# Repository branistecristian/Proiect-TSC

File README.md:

# OpenBook – E-Reader Hardware Project

OpenBook is an open-source e-reader built around the ESP32-C6, featuring a 7.5" e-Paper display, rechargeable battery, and Wi-Fi support. Designed for low-power embedded use and comfortable digital reading.

---

##  Block Diagram

`Images/block_diagram.png`

> Diagram shows how ESP32-C6 is connected to display, battery, charging module, and buttons.

---

## 📋 Bill of Materials (BOM)

| Reference    | Value            | Device                            | Footprint      | Description                      | Link                                                                                             |
|:-------------|:-----------------|:----------------------------------|:---------------|:---------------------------------|:-------------------------------------------------------------------------------------------------|
| BOOT_BUTTON  | BUTTON_CUSYOMV1  | BUTTON_CUSYOMV1                   | MYBUTTON       | -                                | https://industry.panasonic.com/global/en/products/control/switch/light-touch/number/evqpuj02k    |
| C1           | 100nF            | ESP32_WROVER_EAGLE-LTSPICE_CC0402 | C0402          | CAPACITOR, European symbol       | https://componentsearchengine.com/part-view/CC0402MRX5R5BB106/YAGEO                              |
| C2           | 100nF            | ESP32_WROVER_EAGLE-LTSPICE_CC0402 | C0402          | CAPACITOR, European symbol       |                                                                                                  |
| C3           | 100uF TANT       | RCL_CPOL-EUCT3528                 | CT3528         | POLARIZED CAPACITOR              |                                                                                                  |
| C10_SUPERCAP | CPH3225A         | CPH3225A                          | CAPCP3225X100N | 11 mF (EDLC) Supercapacitor 3.3V | https://www.snapeda.com/parts/CPH3225A/Seiko+Instruments/view-part/?ref=eda                      |
| CHG_LED      | -                | ADAFRUIT_LEDCHIP-LED0603          | LED0603        | LED                              | https://www.snapeda.com/parts/KP-1608SURCK/Kingbright/view-part/?ref=search&t=LED                |
| D1           | USBLC6-2SC6Y     | USBLC6-2SC6Y                      | SOT23-6        | TVS Diode Array                  | https://www.snapeda.com/parts/USBLC6-2SC6Y/STMicroelectronics/view-part/?ref=eda                 |
| D2           | -                | AVX_SD0805S020S1R0                | 0805           | Schottky Diode                   | https://eu.mouser.com/ProductDetail/KYOCERA-AVX/SD0805S020S1R0                                   |
| D3           | MBR0530          | MBR0530                           | SOD123         | Schottky Diode                   | https://www.snapeda.com/parts/MBR0530/Onsemi/view-part/?ref=eda                                  |
| D4           | MBR0530          | MBR0530                           | SOD123         | Schottky Diode                   | https://www.snapeda.com/parts/MBR0530/Onsemi/view-part/?ref=eda                                  |
| D5           | MBR0530          | MBR0530                           | SOD123         | Schottky Diode                   | https://www.snapeda.com/parts/MBR0530/Onsemi/view-part/?ref=eda                                  |
| D6           | PGB1010603MR     | PGB1010603MR                      | 0603           | TVS Diode Clamp                  | https://www.snapeda.com/parts/PGB1010603MR/Littelfuse/view-part/?ref=eda                         |
| D7           | -                | AVX_SD0805S020S1R0                | 0805           | Schottky Diode                   | https://eu.mouser.com/ProductDetail/KYOCERA-AVX/SD0805S020S1R0                                   |
| D8           | PGB1010603MR     | PGB1010603MR                      | 0603           | TVS Diode Clamp                  | https://www.snapeda.com/parts/PGB1010603MR/Littelfuse/view-part/?ref=eda                         |
| D9           | PGB1010603MR     | PGB1010603MR                      | 0603           | TVS Diode Clamp                  | https://www.snapeda.com/parts/PGB1010603MR/Littelfuse/view-part/?ref=eda                         |
| D10          | PGB1010603MR     | PGB1010603MR                      | 0603           | TVS Diode Clamp                  | https://www.snapeda.com/parts/PGB1010603MR/Littelfuse/view-part/?ref=eda                         |
| D11          | PGB1010603MR     | PGB1010603MR                      | 0603           | TVS Diode Clamp                  | https://www.snapeda.com/parts/PGB1010603MR/Littelfuse/view-part/?ref=eda                         |
| IC1          | BD5229G-TR       | BD5229G-TR                        | SOT23-5        | Voltage Detector                 | https://componentsearchengine.com/part-view/BD5229G-TR/ROHM%20Semiconductor                      |
| IC4          | XC6220A331MR-G   | XC6220A331MR-G                    | SOT23-5        | LDO Regulator                    | https://componentsearchengine.com/part-view/XC6220A331MR-G/Torex                                 |
| J1           | FFC 24P          | FH34SRJ-24S-0.5SH                 | 0.5mm Pitch    | FFC/FPC Connector                | https://componentsearchengine.com/part-view/FH34SRJ-24S-0.5SH(99)/Hirose                         |
| J2           | USB-C            | USB4110-GF-A                      | USB4110        | USB Type-C Connector             | https://componentsearchengine.com/part-view/USB4110-GF-A/GCT%20(GLOBAL%20CONNECTOR%20TECHNOLOGY) |
| J3           | QWIIC            | QWIIC_CONNECTORJS-1MM             | JST04          | QWIIC I2C Connector              |                                                                                                  |
| J4           | SD Card          | 112A-TAAR-R03_ATTEND              | MicroSD        | MicroSD Socket                   | https://store.comet.srl.ro/Catalogue/Product/43497/                                              |
| L1           | 68uH             | 744043680                         | IND_4828       | Power Inductor                   | https://eu.mouser.com/ProductDetail/Wurth-Elektronik/744043680                                   |
| PFMF.050.1   | -                | ESP32C6_VARISTOR                  | 1812           | Varistor                         | https://www.mouser.co.uk/ProductDetail/EPCOS-TDK/B72520T0350K062                                 |
| Q1           | -                | DMG2305UX-7                       | SOT23          | P-channel MOSFET                 | https://componentsearchengine.com/part-view/DMG2305UX-7/Diodes%20Incorporated                    |
| Q2           | -                | DMG2305UX-7                       | SOT23          | P-channel MOSFET                 |                                                                                                  |
| Q3           | SI1308EDL-T1-GE3 | SI1308EDL                         | SC70           | N-channel MOSFET                 | https://componentsearchengine.com/part-view/SI1308EDL-T1-GE3/Vishay                              |
| R1           | 10K              | ESP32_WROVER_EAGLE-LTSPICE_RR0402 | R0402          | RESISTOR                         |                                                                                                  |
| R2           | 2.2              | ESP32_WROVER_EAGLE-LTSPICE_RR0402 | R0402          | RESISTOR                         | https://componentsearchengine.com/part-view/R0402%201%25%20100%20K%20(RC0402FR-07100KL)/YAGEO    |

---

##  Detailed Hardware Functionality

###  Power System
- 3.7V 1800mAh Li-Po Battery (Cellevia LP584174)
- Charged via TP4056 USB module
- 3.3V provided via AMS1117 LDO regulator

###  Display
- Waveshare 7.5" e-Paper V2, SPI interface
- 800x480 resolution, ultra-low power
- Controlled by ESP32-C6 using GPIOs

###  Microcontroller – ESP32-C6
- BLE 5 + Wi-Fi 6
- Handles display updates and user input
- SPI + UART + GPIO used

###  Estimated Power Budget
| State           | Current | Est. Battery Life (1800mAh) |
|-----------------|---------|------------------------------|
| Idle            | ~20mA   | ~90 hours                    |
| Display Update  | ~120mA  | ~12–15 hours                 |

##  ESP32-C6 Pin Mapping

| Feature          | ESP32-C6 Pin | Description                |
|------------------|--------------|----------------------------|
| SPI CLK          | GPIO6        | Display SCK                |
| SPI MOSI         | GPIO7        | Display data               |
| Display CS       | GPIO10       | Chip select                |
| Display DC       | GPIO5        | Command/data               |
| Display RST      | GPIO4        | Reset                      |
| Display BUSY     | GPIO3        | Ready state                |
| Button A         | GPIO0        | Pull-down                  |
| Button B         | GPIO1        | Pull-down                  |
| UART TX          | GPIO21       | Debug                      |
| UART RX          | GPIO20       | Debug                      |

---

##  Renders & Images

 See `Images/` folder:
- `render_device.png` – Full device
- `render_pcb.png` – PCB only
- `block_diagram.png` – System layout

---

##  Design Notes
- All components were placed in Fusion 360 with correct dimensions
- PCB designed in Eagle + validated via 3D overlay
- Gerbers, BOM, and Pick & Place ready for fab
- Fusion file exported as both `.step` and `.f3d`

---

## Credits

Made with CAD, curse words, and caffeine.

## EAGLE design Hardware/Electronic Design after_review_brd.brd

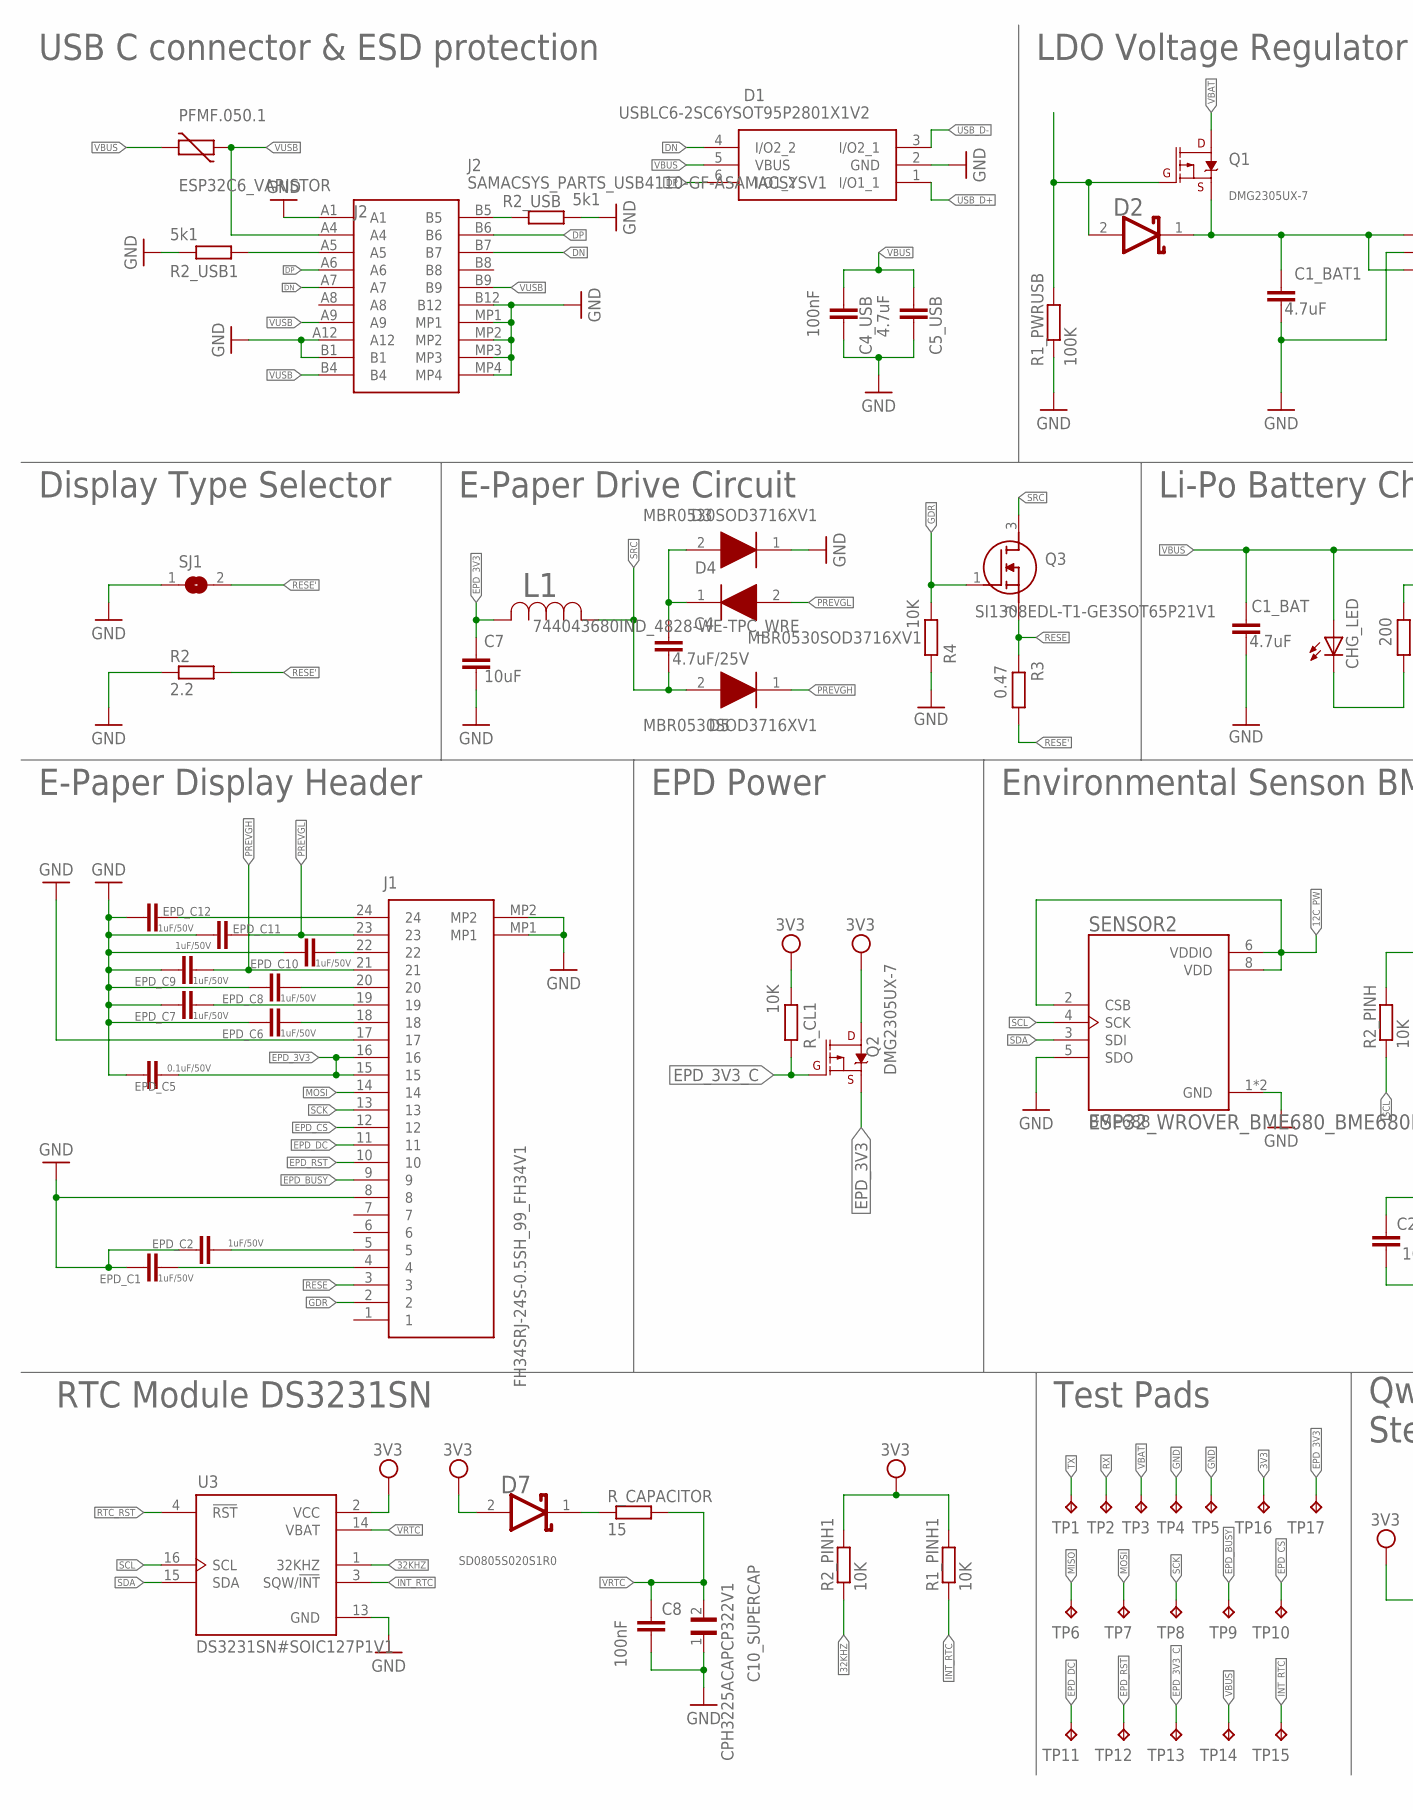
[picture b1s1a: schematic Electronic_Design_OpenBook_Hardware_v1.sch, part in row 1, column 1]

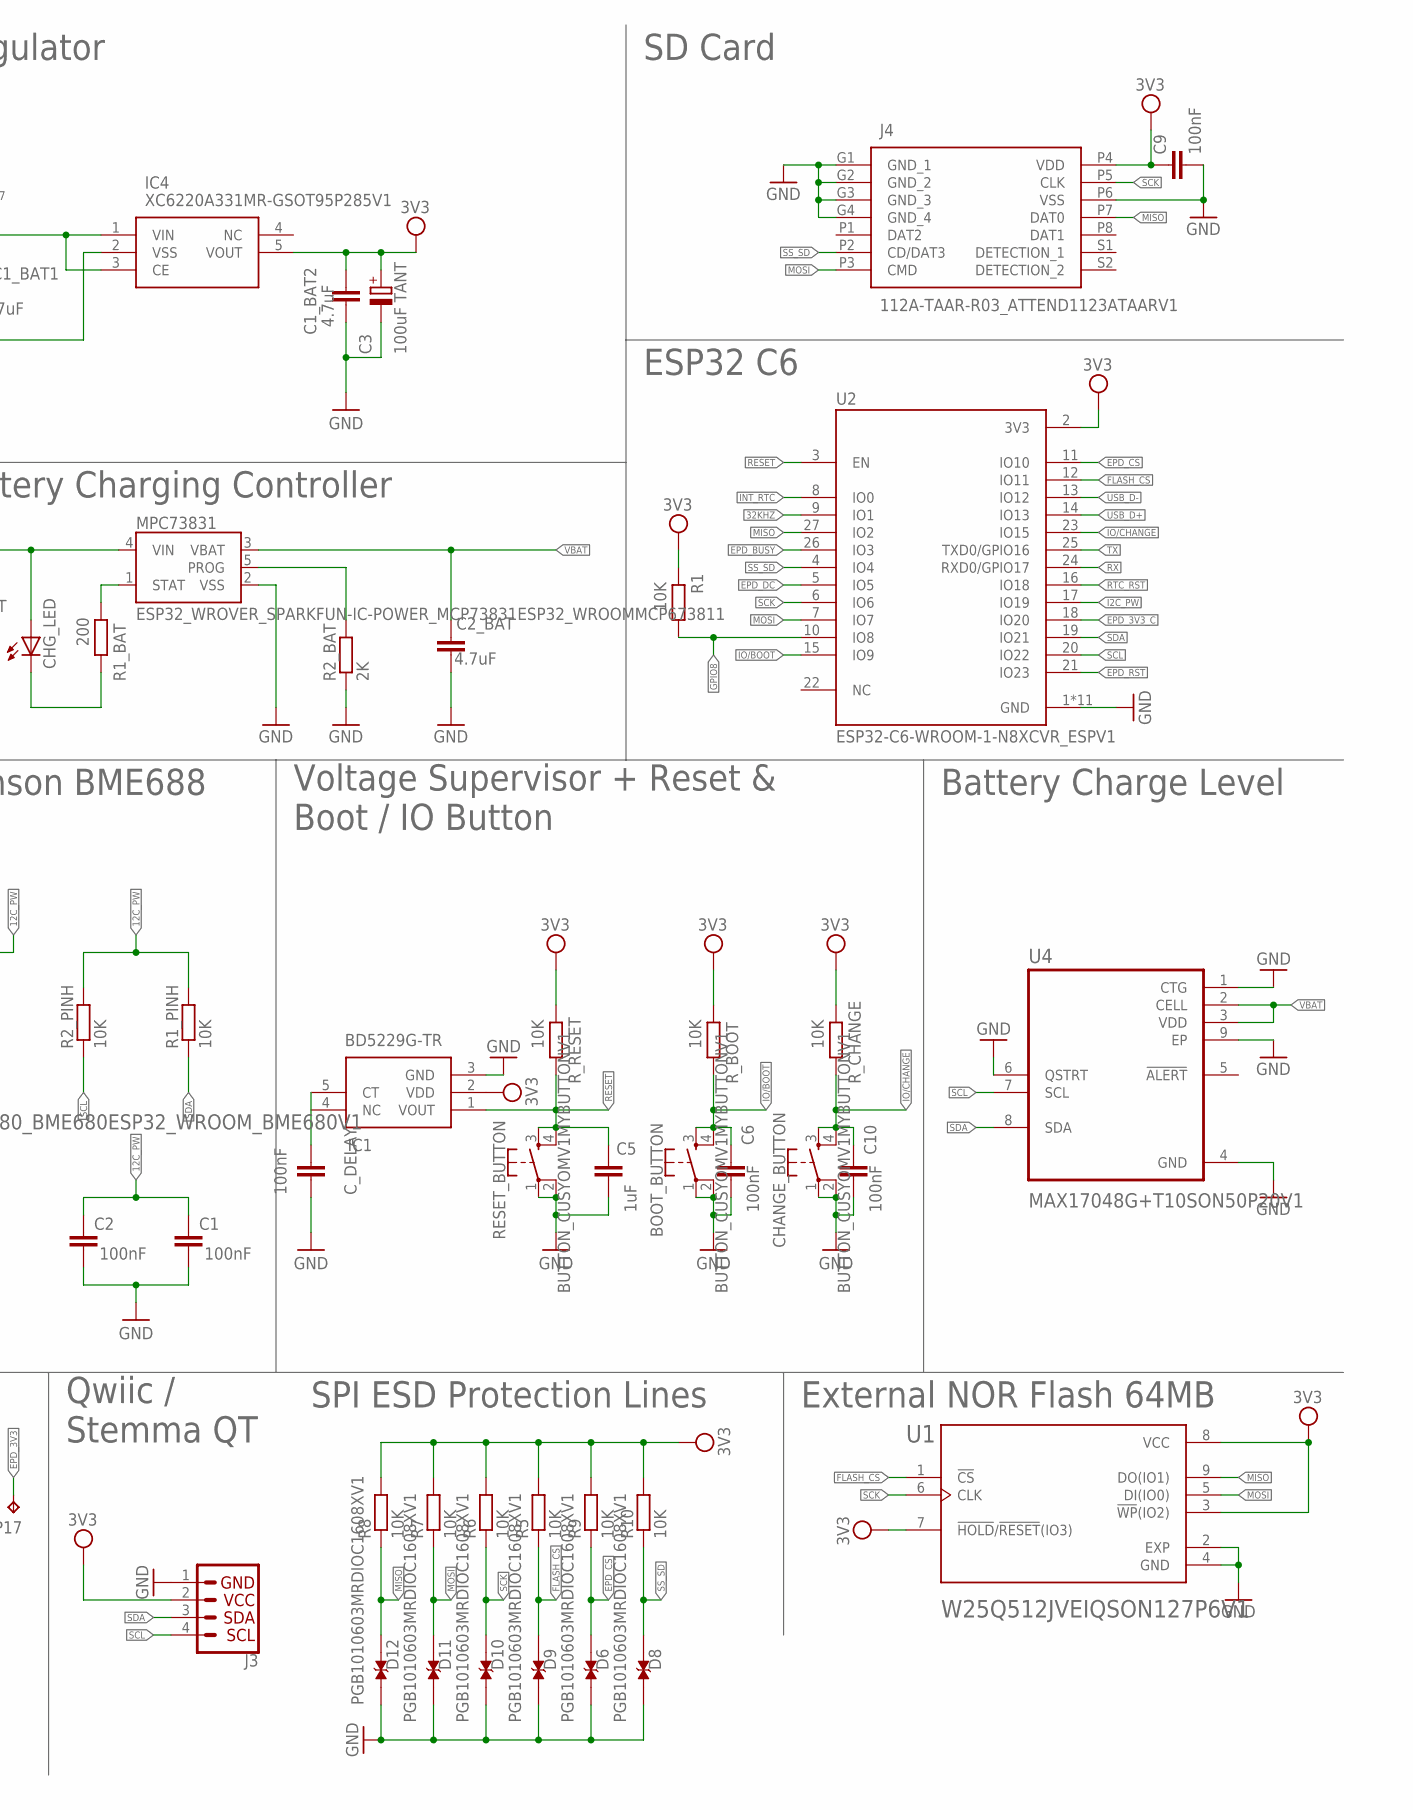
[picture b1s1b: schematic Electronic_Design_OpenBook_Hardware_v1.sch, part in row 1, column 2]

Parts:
BOOT_BUTTON: BUTTON_CUSYOMV1MYBUTTONV1; MYBUTTON
C1, C2, C6, C8, C10: 100nF; EAGLE-LTSPICE_C0402
C1_BAT, C1_BAT1, C1_BAT2, C2_BAT, C5_USB: 4.7uF; ESP32_WROVER_EAGLE-LTSPICE_C0402
C3: 100uF TANT; RCL_CT3528
C4: 4.7uF/25V; ESP32_WROVER_EAGLE-LTSPICE_C0402
C4_USB, C9: 100nF; ESP32_WROVER_EAGLE-LTSPICE_C0402
C5: 1uF; EAGLE-LTSPICE_C0402
C7: 10uF; ESP32_WROVER_EAGLE-LTSPICE_C0402
C10_SUPERCAP: CPH3225ACAPCP322V1; CAPCP3225X100N
CHANGE_BUTTON: BUTTON_CUSYOMV1MYBUTTONV1; MYBUTTON
CHG_LED: ADAFRUIT_LED; ADAFRUIT_CHIP-LED0603
C_DELAY: 100nF; EAGLE-LTSPICE_C0402
D1: USBLC6-2SC6YSOT95P2801X1V2; SOT95P280X145-6N
D2, D7: ESP32_WROVER_AVX---SD0805S020S1R0_AVX_SD0805S020S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; ESP32_WROVER_AVX---SD0805S020S1R0_AVX_SD0805S020S1R0_0
D3, D4, D5: MBR0530SOD3716XV1; SOD3716X135N
D6, D8, D9, D10, D11, D12: PGB1010603MRDIOC1608XV1; DIOC1608X36N
EPD_C1, EPD_C2, EPD_C6, EPD_C7, EPD_C8, EPD_C9, EPD_C10, EPD_C11, EPD_C12: 1uF/50V; EAGLE-LTSPICE_C0402
EPD_C5: 0.1uF/50V; EAGLE-LTSPICE_C0402
IC1: BD5229G-TR; SOT95P280X120-5N
IC4: XC6220A331MR-GSOT95P285V1; SOT95P280X120-5N
J1: FH34SRJ-24S-0.5SH_99_FH34V1; FH34SRJ24S05SH99
J2: SAMACSYS_PARTS_USB4110-GF-ASAMACSYSV1; SAMACSYS_PARTS_USB4110GFA
J3: QWIIC_RIGHT_ANGLE; JST04_1MM_RA
J4: 112A-TAAR-R03_ATTEND1123ATAARV1; 112ATAARR03ATTEND
L1: 744043680IND_4828-WE-TPC_WRE; IND_4828-WE-TPC_WRE
MPC73831: ESP32_WROVER_SPARKFUN-IC-POWER_MCP73831ESP32_WROO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; ESP32_WROVER_SPARKFUN-IC-POWER_SOT23-5
PFMF.050.1: ESP32C6_VARISTOR; ESP32C6_VARISTOR_CT/CN1812
Q1, Q2: 20V/4.2A/52mΩ/1.4W; ESP32_WROVER_SPARKFUN-DISCRETESEMI_SOT23-3
Q3: SI1308EDL-T1-GE3SOT65P21V1; SOT65P210X110-3N
R1, R1_PINH, R1_PINH1, R2_PINH, R2_PINH1, R4, R5, R6, R7, R8, R9, R10: 10K; ESP32_WROVER_EAGLE-LTSPICE_R0402
R1_BAT: 200; ESP32_WROVER_EAGLE-LTSPICE_R0402
R1_PWRUSB: 100K; ESP32_WROVER_EAGLE-LTSPICE_R0402
R2: 2.2; ESP32_WROVER_EAGLE-LTSPICE_R0402
R2_BAT: 2K; ESP32_WROVER_EAGLE-LTSPICE_R0402
R2_USB, R2_USB1: 5k1; ESP32_WROVER_EAGLE-LTSPICE_R0402
R3: 0.47; ESP32_WROVER_EAGLE-LTSPICE_R0402
RESET_BUTTON: BUTTON_CUSYOMV1MYBUTTONV1; MYBUTTON
R_BOOT: 10K; ESP32_WROVER_EAGLE-LTSPICE_R0402
R_CAPACITOR: 15; ESP32_WROVER_EAGLE-LTSPICE_R0402
R_CHANGE: 10K; ESP32_WROVER_EAGLE-LTSPICE_R0402
R_CL1: 10K; ESP32_WROVER_EAGLE-LTSPICE_R0402
R_RESET: 10K; ESP32_WROVER_EAGLE-LTSPICE_R0402
SENSOR2: ESP32_WROVER_BME680_BME680ESP32_WROOM_BME680V1; ESP32_WROVER_BME680_PSON80P300X300X100-8N
SJ1: SJSJV1; SJ
TP1, TP2, TP3, TP4, TP5, TP6, TP7, TP8, TP9, TP10, TP11, TP12, TP13, TP14, TP15, TP16, TP17: TPTP20R; TP20R
U1: W25Q512JVEIQSON127P6V1; SON127P600X800X80-9N
U2: ESP32-C6-WROOM-1-N8XCVR_ESPV1; XCVR_ESP32-C6-WROOM-1-N8
U3: DS3231SN#SOIC127P1V1; SOIC127P1032X265-16N
U4: MAX17048G+T10SON50P20V1; SON50P200X200X80-9N

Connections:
3V3: C1_BAT2.1, C3.+, C9.1, D7.2 (ANODE), IC1.2 (VDD), IC4.5 (VOUT), J3.2, J4.P4 (VDD), Q2.3 (D), R1.2, R1_PINH1.2, R2_PINH1.2, R5.2, R6.2, R7.2, R8.2, R9.2, R10.2, R_BOOT.2, R_CHANGE.2, R_CL1.2, R_RESET.2, TP16.TP, U1.3 (!WP!(IO2)), U1.7 (!HOLD!/!RESET!(IO3)), U1.8 (VCC), U2.2 (3V3), U3.2 (VCC)
12C_PW: C1.1, C2.1, R1_PINH.2, R2_PINH.2, SENSOR2.2 (CSB), SENSOR2.6 (VDDIO), SENSOR2.8 (VDD)
32KHZ: R2_PINH1.1, U2.9 (IO1), U3.1 (32KHZ)
DN: D1.4 (I/O2_2), J2.A7, J2.B7
DP: D1.6 (I/O1_2), J2.A6, J2.B6
EPD_3V3: C7.1, EPD_C5.2, J1.15, J1.16, L1.2, Q2.2 (S), TP17.TP
EPD_3V3_C: Q2.1 (G), R_CL1.1, TP13.TP, U2.18 (IO20)
EPD_BUSY: J1.9, TP9.TP, U2.26 (IO3)
EPD_CS: D6.2, J1.12, R9.1, TP10.TP, U2.11 (IO10)
EPD_DC: J1.11, TP11.TP, U2.5 (IO5)
EPD_RST: J1.10, TP12.TP, U2.21 (IO23)
FLASH_CS: D9.2, R5.1, U1.1 (!CS), U2.12 (IO11)
GDR: J1.2, Q3.1 (G), R4.2
GND: BOOT_BUTTON.1, BOOT_BUTTON.2, C1.2, C1_BAT.2, C1_BAT1.2, C1_BAT2.2, C2.2, C2_BAT.2, C3.-, C4_USB.2, C5.2, C5_USB.2, C6.2, C7.2, C8.2, C9.2, C10.2, C10_SUPERCAP.1, CHANGE_BUTTON.1, CHANGE_BUTTON.2, C_DELAY.2, D1.2 (GND), D3.1 (K), D6.1, D8.1, D9.1, D10.1, D11.1, D12.1, EPD_C1.1, EPD_C2.1, EPD_C5.1, EPD_C6.1, EPD_C7.1, EPD_C8.1, EPD_C9.1, EPD_C10.1, EPD_C11.1, EPD_C12.1, IC1.3 (GND), IC4.2 (VSS), J1.8, J1.17, J1.MP1, J1.MP2, J2.A1, J2.A12, J2.B1, J2.B12, J2.MP1, J2.MP2, J2.MP3, J2.MP4, J3.1, J4.G1 (GND_1), J4.G2 (GND_2), J4.G3 (GND_3), J4.G4 (GND_4), J4.P6 (VSS), MPC73831.2 (VSS), R1_PWRUSB.1, R2.1, R2_BAT.1, R2_USB.2, R2_USB1.1, R4.1, RESET_BUTTON.1, RESET_BUTTON.2, SENSOR2.1 (GND), SENSOR2.5 (SDO), SENSOR2.7 (GND), SJ1.1, TP4.TP, TP5.TP, U1.2 (EXP), U1.4 (GND), U2.1 (GND), U2.28 (GND), U2.29_1 (GND), U2.29_2 (GND), U2.29_3 (GND), U2.29_4 (GND), U2.29_5 (GND), U2.29_6 (GND), U2.29_7 (GND), U2.29_8 (GND), U2.29_9 (GND), U3.13 (GND), U4.1 (CTG), U4.4 (GND), U4.6 (QSTRT), U4.9 (EP)
GPIO8: R1.1, U2.10 (IO8)
I2C_PW: U2.17 (IO19)
INT_RTC: R1_PINH1.1, TP15.TP, U2.8 (IO0), U3.3 (SQW/!INT)
IO/BOOT: BOOT_BUTTON.3, BOOT_BUTTON.4, C6.1, R_BOOT.1, U2.15 (IO9)
IO/CHANGE: C10.1, CHANGE_BUTTON.3, CHANGE_BUTTON.4, R_CHANGE.1, U2.23 (IO15)
MISO: D12.2, J4.P7 (DAT0), R8.1, TP6.TP, U1.9 (DO(IO1)), U2.27 (IO2)
MOSI: D11.2, J1.14, J4.P3 (CMD), R7.1, TP7.TP, U1.5 (DI(IO0)), U2.7 (IO7)
unnamed: J2.A5, R2_USB1.2
unnamed: C4.1, D3.2 (A), D4.1 (K)
unnamed: C_DELAY.1, IC1.5 (CT)
unnamed: CHG_LED.C, R1_BAT.1
unnamed: MPC73831.1 (STAT), R1_BAT.2
unnamed: J2.B5, R2_USB.1
unnamed: MPC73831.5 (PROG), R2_BAT.2
unnamed: EPD_C2.2, J1.5
unnamed: EPD_C1.2, J1.4
unnamed: EPD_C12.2, J1.24
unnamed: EPD_C10.2, J1.22
unnamed: EPD_C8.2, J1.20
unnamed: EPD_C7.2, J1.19
unnamed: EPD_C6.2, J1.18
unnamed: D7.1 (CATHODE), R_CAPACITOR.1
unnamed: D2.2 (ANODE), Q1.1 (G), R1_PWRUSB.2
unnamed: C1_BAT1.1, D2.1 (CATHODE), IC4.1 (VIN), IC4.3 (CE), Q1.2 (S)
PREVGH: D5.1 (K), EPD_C9.2, J1.21
PREVGL: D4.2 (A), EPD_C11.2, J1.23
RESE: J1.3, Q3.2 (S), R3.2
RESE': R2.2, R3.1, SJ1.2
RESET: C5.1, IC1.1 (VOUT), RESET_BUTTON.3, RESET_BUTTON.4, R_RESET.1, U2.3 (EN)
RTC_RST: U2.16 (IO18), U3.4 (!RST)
RX: TP2.TP, U2.24 (RXD0/GPIO17)
SCK: D10.2, J1.13, J4.P5 (CLK), R6.1, TP8.TP, U1.6 (CLK), U2.6 (IO6)
SCL: J3.4, R2_PINH.1, SENSOR2.4 (SCK), U2.20 (IO22), U3.16 (SCL), U4.7 (SCL)
SDA: J3.3, R1_PINH.1, SENSOR2.3 (SDI), U2.19 (IO21), U3.15 (SDA), U4.8 (SDA)
SRC: C4.2, D5.2 (A), L1.1, Q3.3 (D)
SS_SD: D8.2, J4.P2 (CD/DAT3), R10.1, U2.4 (IO4)
TX: TP1.TP, U2.25 (TXD0/GPIO16)
USB_D+: D1.1 (I/O1_1), U2.14 (IO13)
USB_D-: D1.3 (I/O2_1), U2.13 (IO12)
VBAT: C2_BAT.1, MPC73831.3 (VBAT), Q1.3 (D), TP3.TP, U4.2 (CELL), U4.3 (VDD)
VBUS: C1_BAT.1, C4_USB.1, C5_USB.1, CHG_LED.A, D1.5 (VBUS), MPC73831.4 (VIN), PFMF.050.1.2, TP14.TP
VRTC: C8.1, C10_SUPERCAP.2, R_CAPACITOR.2, U3.14 (VBAT)
VUSB: J2.A4, J2.A9, J2.B4, J2.B9, PFMF.050.1.1

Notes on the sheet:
USB C connector & ESD protection
Display Type Selector
E-Paper Display Header
RTC Module DS3231SN
SD0805S020S1R0
LDO Voltage Regulator
DMG2305UX-7
E-Paper Drive Circuit
EPD Power
Environmental Senson BME688
BME688
Test Pads
Qwiic / Stemma QT
SPI ESD Protection Lines
External NOR Flash 64MB
Voltage Supervisor + Reset & Boot / IO Button
Battery Charge Level
Li-Po Battery Charging Controller
SD Card
ESP32 C6

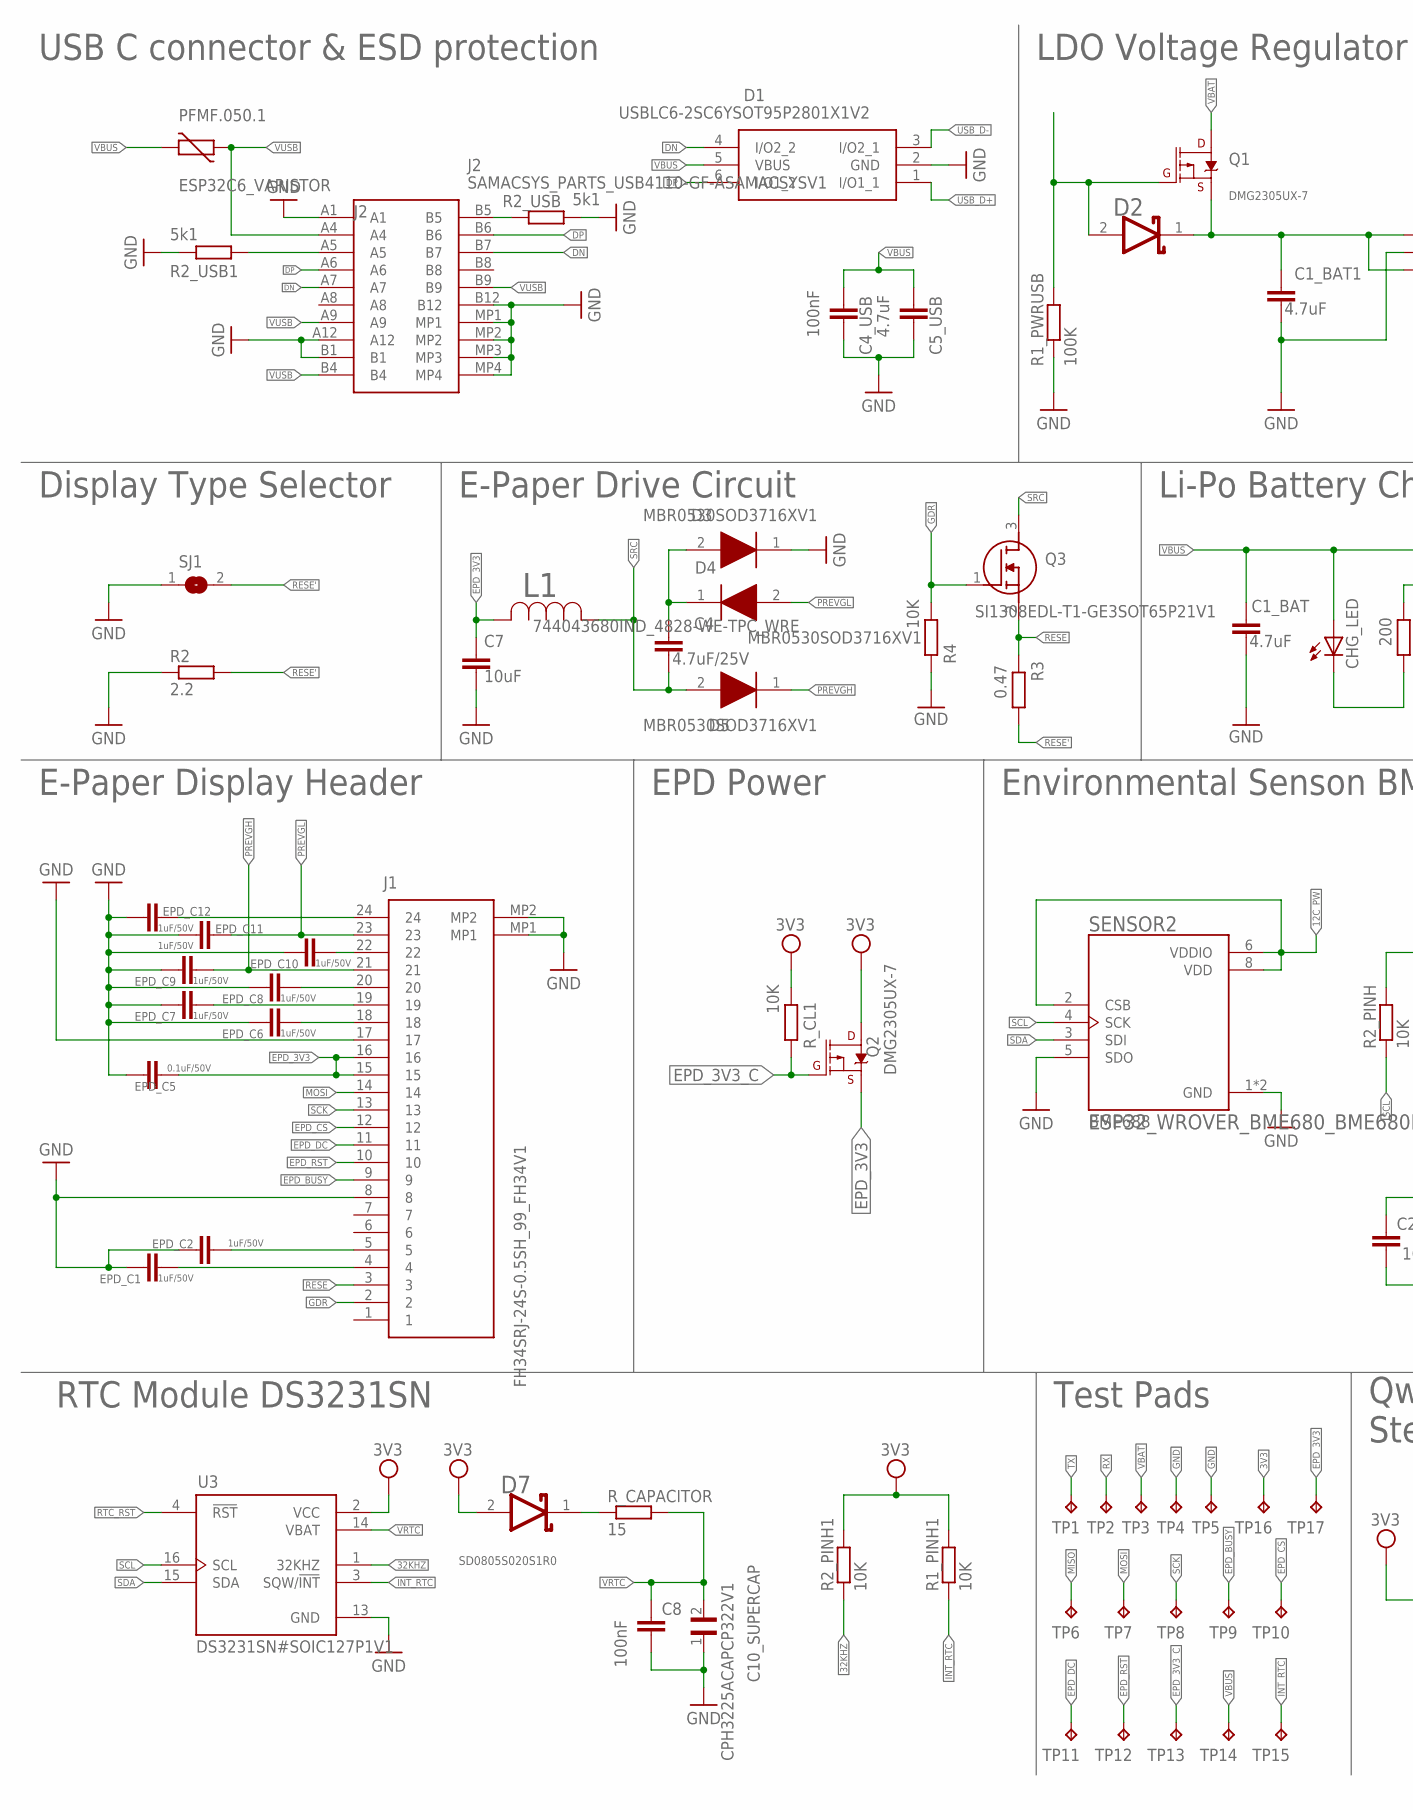
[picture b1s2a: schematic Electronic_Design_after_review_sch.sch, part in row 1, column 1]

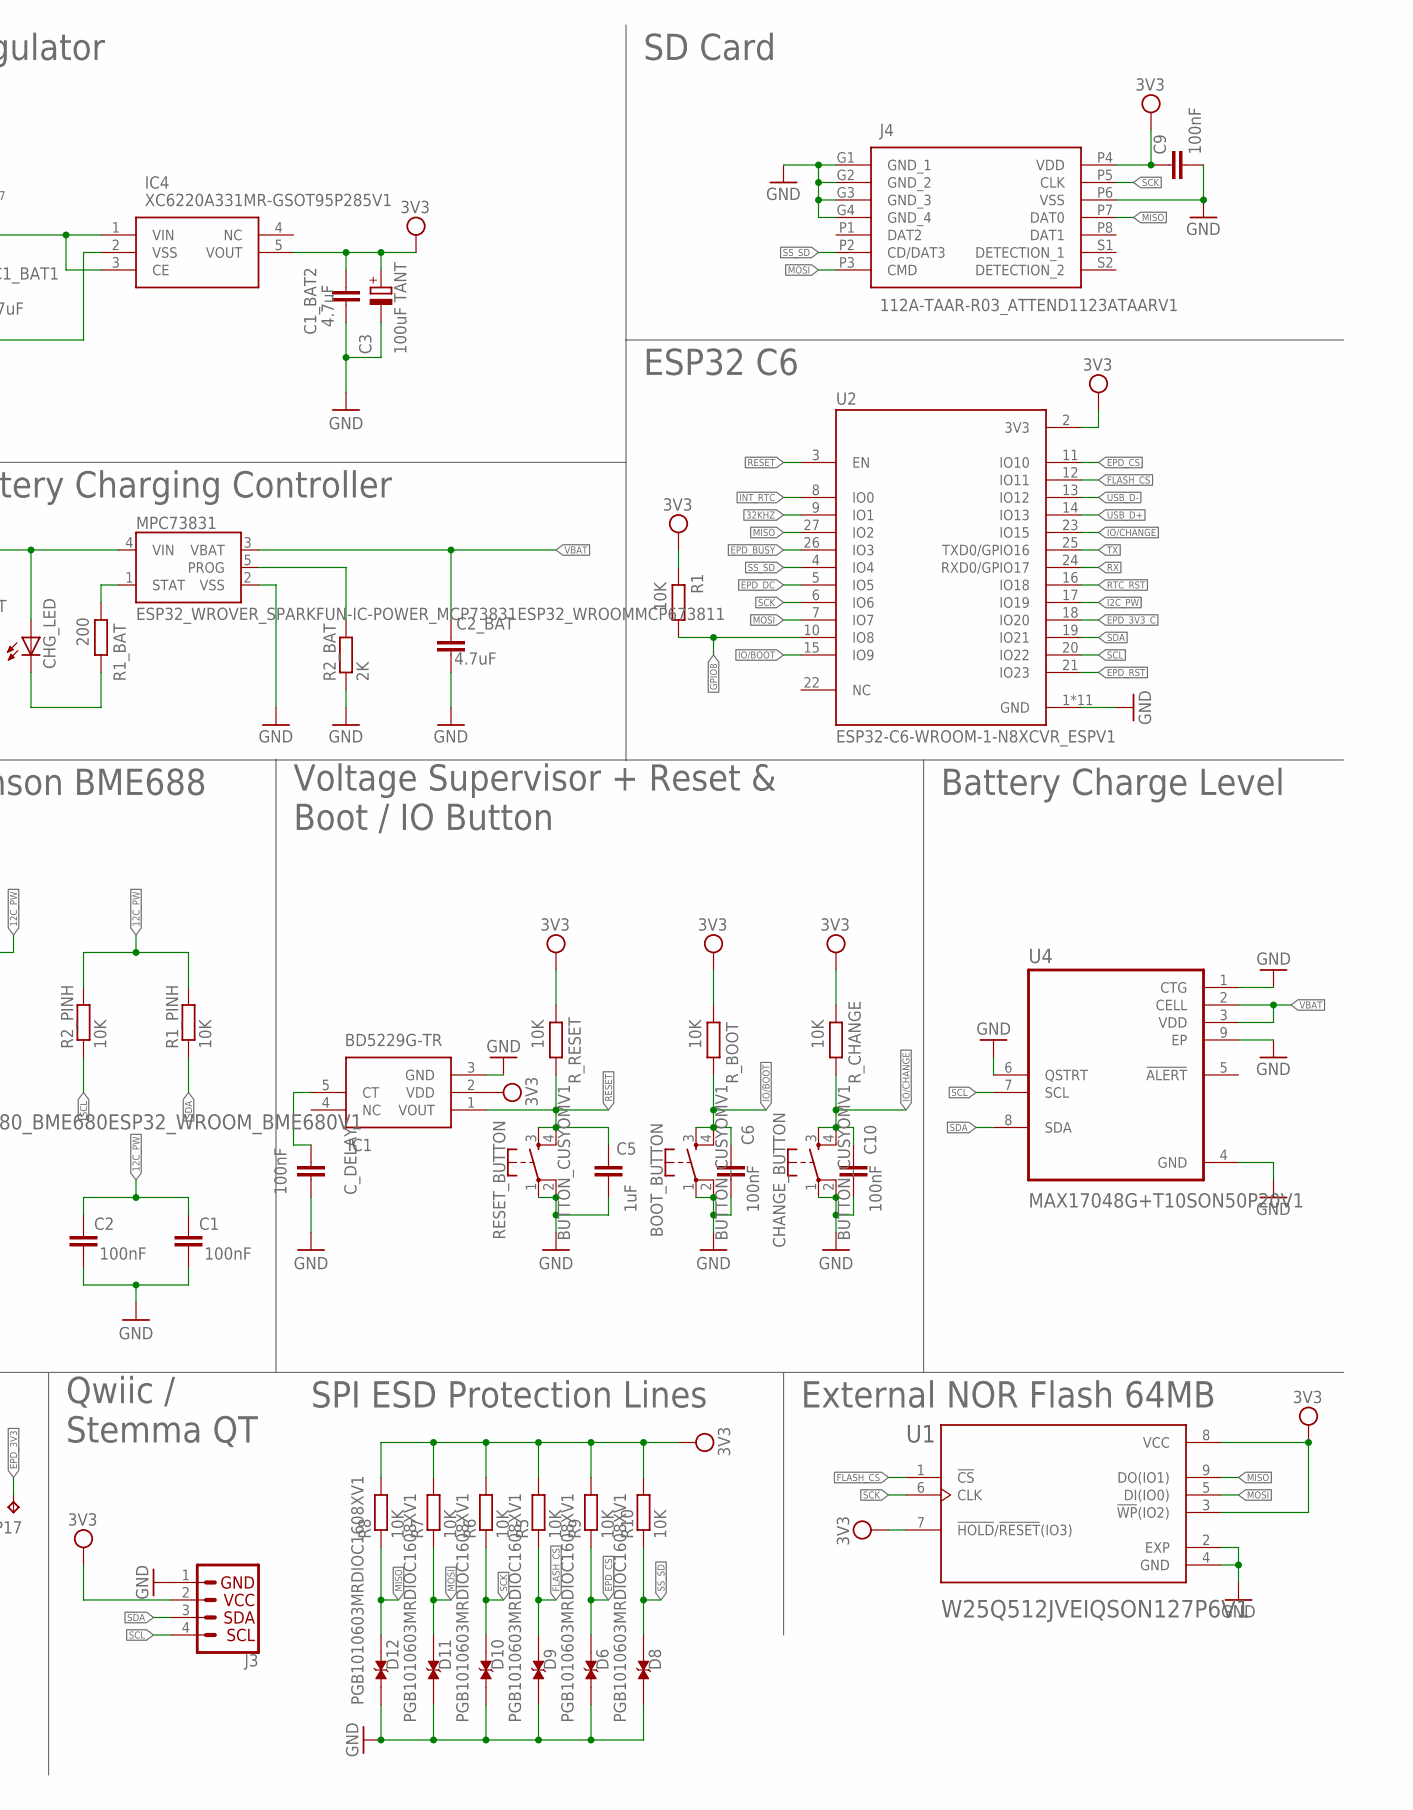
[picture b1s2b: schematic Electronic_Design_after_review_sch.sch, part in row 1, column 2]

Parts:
BOOT_BUTTON: BUTTON_CUSYOMV1; MYBUTTON
C1, C2, C6, C8, C10: 100nF; EAGLE-LTSPICE_C0402
C1_BAT, C1_BAT1, C1_BAT2, C2_BAT, C5_USB: 4.7uF; ESP32_WROVER_EAGLE-LTSPICE_C0402
C3: 100uF TANT; RCL_CT3528
C4: 4.7uF/25V; ESP32_WROVER_EAGLE-LTSPICE_C0402
C4_USB, C9: 100nF; ESP32_WROVER_EAGLE-LTSPICE_C0402
C5: 1uF; EAGLE-LTSPICE_C0402
C7: 10uF; ESP32_WROVER_EAGLE-LTSPICE_C0402
C10_SUPERCAP: CPH3225ACAPCP322V1; CAPCP3225X100N
CHANGE_BUTTON: BUTTON_CUSYOMV1; MYBUTTON
CHG_LED: ADAFRUIT_LED; ADAFRUIT_CHIP-LED0603
C_DELAY: 100nF; EAGLE-LTSPICE_C0402
D1: USBLC6-2SC6YSOT95P2801X1V2; SOT95P280X145-6N
D2, D7: ESP32_WROVER_AVX---SD0805S020S1R0_AVX_SD0805S020S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; ESP32_WROVER_AVX---SD0805S020S1R0_AVX_SD0805S020S1R0_0
D3, D4, D5: MBR0530SOD3716XV1; SOD3716X135N
D6, D8, D9, D10, D11, D12: PGB1010603MRDIOC1608XV1; DIOC1608X36N
EPD_C1, EPD_C2, EPD_C6, EPD_C7, EPD_C8, EPD_C9, EPD_C10, EPD_C11, EPD_C12: 1uF/50V; EAGLE-LTSPICE_C0402
EPD_C5: 0.1uF/50V; EAGLE-LTSPICE_C0402
IC1: BD5229G-TR; SOT95P280X120-5N
IC4: XC6220A331MR-GSOT95P285V1; SOT95P280X120-5N
J1: FH34SRJ-24S-0.5SH_99_FH34V1; FH34SRJ24S05SH99
J2: SAMACSYS_PARTS_USB4110-GF-ASAMACSYSV1; SAMACSYS_PARTS_USB4110GFA
J3: QWIIC_RIGHT_ANGLE; JST04_1MM_RA
J4: 112A-TAAR-R03_ATTEND1123ATAARV1; 112ATAARR03ATTEND
L1: 744043680IND_4828-WE-TPC_WRE; IND_4828-WE-TPC_WRE
MPC73831: ESP32_WROVER_SPARKFUN-IC-POWER_MCP73831ESP32_WROO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; ESP32_WROVER_SPARKFUN-IC-POWER_SOT23-5
PFMF.050.1: ESP32C6_VARISTOR; ESP32C6_VARISTOR_CT/CN1812
Q1, Q2: 20V/4.2A/52mΩ/1.4W; ESP32_WROVER_SPARKFUN-DISCRETESEMI_SOT23-3
Q3: SI1308EDL-T1-GE3SOT65P21V1; SOT65P210X110-3N
R1, R1_PINH, R1_PINH1, R2_PINH, R2_PINH1, R4, R5, R6, R7, R8, R9, R10: 10K; ESP32_WROVER_EAGLE-LTSPICE_R0402
R1_BAT: 200; ESP32_WROVER_EAGLE-LTSPICE_R0402
R1_PWRUSB: 100K; ESP32_WROVER_EAGLE-LTSPICE_R0402
R2: 2.2; ESP32_WROVER_EAGLE-LTSPICE_R0402
R2_BAT: 2K; ESP32_WROVER_EAGLE-LTSPICE_R0402
R2_USB, R2_USB1: 5k1; ESP32_WROVER_EAGLE-LTSPICE_R0402
R3: 0.47; ESP32_WROVER_EAGLE-LTSPICE_R0402
RESET_BUTTON: BUTTON_CUSYOMV1; MYBUTTON
R_BOOT: 10K; ESP32_WROVER_EAGLE-LTSPICE_R0402
R_CAPACITOR: 15; ESP32_WROVER_EAGLE-LTSPICE_R0402
R_CHANGE: 10K; ESP32_WROVER_EAGLE-LTSPICE_R0402
R_CL1: 10K; ESP32_WROVER_EAGLE-LTSPICE_R0402
R_RESET: 10K; ESP32_WROVER_EAGLE-LTSPICE_R0402
SENSOR2: ESP32_WROVER_BME680_BME680ESP32_WROOM_BME680V1; ESP32_WROVER_BME680_PSON80P300X300X100-8N
SJ1: SJSJV1; SJ
TP1, TP2, TP3, TP4, TP5, TP6, TP7, TP8, TP9, TP10, TP11, TP12, TP13, TP14, TP15, TP16, TP17: TP; TP20R
U1: W25Q512JVEIQSON127P6V1; SON127P600X800X80-9N
U2: ESP32-C6-WROOM-1-N8XCVR_ESPV1; XCVR_ESP32-C6-WROOM-1-N8
U3: DS3231SN#SOIC127P1V1; SOIC127P1032X265-16N
U4: MAX17048G+T10SON50P20V1; SON50P200X200X80-9N

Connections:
3V3: C1_BAT2.1, C3.+, C9.1, D7.2 (ANODE), IC1.2 (VDD), IC4.5 (VOUT), J3.2, J4.P4 (VDD), Q2.3 (D), R1.2, R1_PINH1.2, R2_PINH1.2, R5.2, R6.2, R7.2, R8.2, R9.2, R10.2, R_BOOT.2, R_CHANGE.2, R_CL1.2, R_RESET.2, TP16.TP, U1.3 (!WP!(IO2)), U1.7 (!HOLD!/!RESET!(IO3)), U1.8 (VCC), U2.2 (3V3), U3.2 (VCC)
12C_PW: C1.1, C2.1, R1_PINH.2, R2_PINH.2, SENSOR2.2 (CSB), SENSOR2.6 (VDDIO), SENSOR2.8 (VDD)
32KHZ: R2_PINH1.1, U2.9 (IO1), U3.1 (32KHZ)
DN: D1.4 (I/O2_2), J2.A7, J2.B7
DP: D1.6 (I/O1_2), J2.A6, J2.B6
EPD_3V3: C7.1, EPD_C5.2, J1.15, J1.16, L1.2, Q2.2 (S), TP17.TP
EPD_3V3_C: Q2.1 (G), R_CL1.1, TP13.TP, U2.18 (IO20)
EPD_BUSY: J1.9, TP9.TP, U2.26 (IO3)
EPD_CS: D6.2, J1.12, R9.1, TP10.TP, U2.11 (IO10)
EPD_DC: J1.11, TP11.TP, U2.5 (IO5)
EPD_RST: J1.10, TP12.TP, U2.21 (IO23)
FLASH_CS: D9.2, R5.1, U1.1 (!CS), U2.12 (IO11)
GDR: J1.2, Q3.1 (G), R4.2
GND: BOOT_BUTTON.1, BOOT_BUTTON.2, C1.2, C1_BAT.2, C1_BAT1.2, C1_BAT2.2, C2.2, C2_BAT.2, C3.-, C4_USB.2, C5.2, C5_USB.2, C6.2, C7.2, C8.2, C9.2, C10.2, C10_SUPERCAP.1, CHANGE_BUTTON.1, CHANGE_BUTTON.2, C_DELAY.2, D1.2 (GND), D3.1 (K), D6.1, D8.1, D9.1, D10.1, D11.1, D12.1, EPD_C1.1, EPD_C2.1, EPD_C5.1, EPD_C6.1, EPD_C7.1, EPD_C8.1, EPD_C9.1, EPD_C10.1, EPD_C11.1, EPD_C12.1, IC1.3 (GND), IC4.2 (VSS), J1.8, J1.17, J1.MP1, J1.MP2, J2.A1, J2.A12, J2.B1, J2.B12, J2.MP1, J2.MP2, J2.MP3, J2.MP4, J3.1, J4.G1 (GND_1), J4.G2 (GND_2), J4.G3 (GND_3), J4.G4 (GND_4), J4.P6 (VSS), MPC73831.2 (VSS), R1_PWRUSB.1, R2.1, R2_BAT.1, R2_USB.2, R2_USB1.1, R4.1, RESET_BUTTON.1, RESET_BUTTON.2, SENSOR2.1 (GND), SENSOR2.5 (SDO), SENSOR2.7 (GND), SJ1.1, TP4.TP, TP5.TP, U1.2 (EXP), U1.4 (GND), U2.1 (GND), U2.28 (GND), U2.29_1 (GND), U2.29_2 (GND), U2.29_3 (GND), U2.29_4 (GND), U2.29_5 (GND), U2.29_6 (GND), U2.29_7 (GND), U2.29_8 (GND), U2.29_9 (GND), U3.13 (GND), U4.1 (CTG), U4.4 (GND), U4.6 (QSTRT), U4.9 (EP)
GPIO8: R1.1, U2.10 (IO8)
I2C_PW: U2.17 (IO19)
INT_RTC: R1_PINH1.1, TP15.TP, U2.8 (IO0), U3.3 (SQW/!INT)
IO/BOOT: BOOT_BUTTON.3, BOOT_BUTTON.4, C6.1, R_BOOT.1, U2.15 (IO9)
IO/CHANGE: C10.1, CHANGE_BUTTON.3, CHANGE_BUTTON.4, R_CHANGE.1, U2.23 (IO15)
MISO: D12.2, J4.P7 (DAT0), R8.1, TP6.TP, U1.9 (DO(IO1)), U2.27 (IO2)
MOSI: D11.2, J1.14, J4.P3 (CMD), R7.1, TP7.TP, U1.5 (DI(IO0)), U2.7 (IO7)
unnamed: J2.A5, R2_USB1.2
unnamed: C4.1, D3.2 (A), D4.1 (K)
unnamed: C_DELAY.1, IC1.5 (CT)
unnamed: CHG_LED.C, R1_BAT.1
unnamed: MPC73831.1 (STAT), R1_BAT.2
unnamed: J2.B5, R2_USB.1
unnamed: MPC73831.5 (PROG), R2_BAT.2
unnamed: EPD_C2.2, J1.5
unnamed: EPD_C1.2, J1.4
unnamed: EPD_C12.2, J1.24
unnamed: EPD_C10.2, J1.22
unnamed: EPD_C8.2, J1.20
unnamed: EPD_C7.2, J1.19
unnamed: EPD_C6.2, J1.18
unnamed: D7.1 (CATHODE), R_CAPACITOR.1
unnamed: D2.2 (ANODE), Q1.1 (G), R1_PWRUSB.2
unnamed: C1_BAT1.1, D2.1 (CATHODE), IC4.1 (VIN), IC4.3 (CE), Q1.2 (S)
PREVGH: D5.1 (K), EPD_C9.2, J1.21
PREVGL: D4.2 (A), EPD_C11.2, J1.23
RESE: J1.3, Q3.2 (S), R3.2
RESE': R2.2, R3.1, SJ1.2
RESET: C5.1, IC1.1 (VOUT), RESET_BUTTON.3, RESET_BUTTON.4, R_RESET.1, U2.3 (EN)
RTC_RST: U2.16 (IO18), U3.4 (!RST)
RX: TP2.TP, U2.24 (RXD0/GPIO17)
SCK: D10.2, J1.13, J4.P5 (CLK), R6.1, TP8.TP, U1.6 (CLK), U2.6 (IO6)
SCL: J3.4, R2_PINH.1, SENSOR2.4 (SCK), U2.20 (IO22), U3.16 (SCL), U4.7 (SCL)
SDA: J3.3, R1_PINH.1, SENSOR2.3 (SDI), U2.19 (IO21), U3.15 (SDA), U4.8 (SDA)
SRC: C4.2, D5.2 (A), L1.1, Q3.3 (D)
SS_SD: D8.2, J4.P2 (CD/DAT3), R10.1, U2.4 (IO4)
TX: TP1.TP, U2.25 (TXD0/GPIO16)
USB_D+: D1.1 (I/O1_1), U2.14 (IO13)
USB_D-: D1.3 (I/O2_1), U2.13 (IO12)
VBAT: C2_BAT.1, MPC73831.3 (VBAT), Q1.3 (D), TP3.TP, U4.2 (CELL), U4.3 (VDD)
VBUS: C1_BAT.1, C4_USB.1, C5_USB.1, CHG_LED.A, D1.5 (VBUS), MPC73831.4 (VIN), PFMF.050.1.2, TP14.TP
VRTC: C8.1, C10_SUPERCAP.2, R_CAPACITOR.2, U3.14 (VBAT)
VUSB: J2.A4, J2.A9, J2.B4, J2.B9, PFMF.050.1.1

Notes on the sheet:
USB C connector & ESD protection
Display Type Selector
E-Paper Display Header
RTC Module DS3231SN
SD0805S020S1R0
LDO Voltage Regulator
DMG2305UX-7
E-Paper Drive Circuit
EPD Power
Environmental Senson BME688
BME688
Test Pads
Qwiic / Stemma QT
SPI ESD Protection Lines
External NOR Flash 64MB
Voltage Supervisor + Reset & Boot / IO Button
Battery Charge Level
Li-Po Battery Charging Controller
SD Card
ESP32 C6

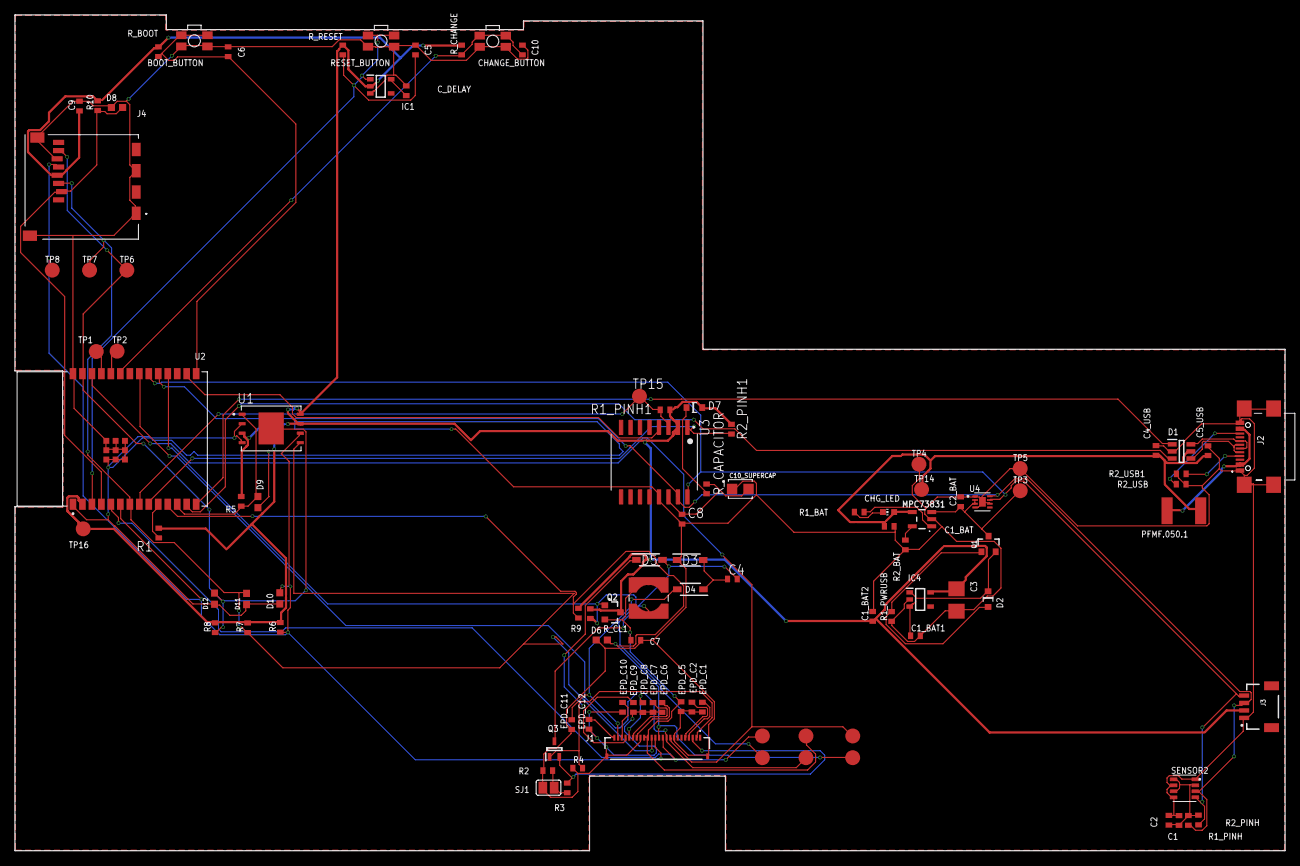
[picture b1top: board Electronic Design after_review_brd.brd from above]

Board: 2 copper layers, 170.2 x 112.0 mm, 103 parts (0 on the bottom side), 56 nets.

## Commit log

2025-04-05 Github OpenBook Project Final Push
2025-04-05 Create LICENSE
2025-04-15 After review
